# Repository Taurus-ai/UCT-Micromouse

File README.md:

# UCT-Micromouse EEE3088F PROJECT 2024 - POWER SUBMODULE
This is a repository for the power subsystem. The power substem is responsible for providing power to the micromouse design.
This design has 4 subcircuits which make up the subsytem:
1. Connectors - These provide interface to the other submodules. 
2. USB Power Supply - This provides external power to the circuit to charge the battery.
3. Battery charger - This cicuit mornitors the battery and charge it.
4. Motor Driver - This is a dual H-bridge motor driver circuit which drives 2 motors at desired current. 

This reporsitory includes the following files:
1. KiCAd project - This has the design of the pcb
2. BOM file - Bill of matertials for the components in the design
3. Datasheets - These are datasheets of the components used in the design.

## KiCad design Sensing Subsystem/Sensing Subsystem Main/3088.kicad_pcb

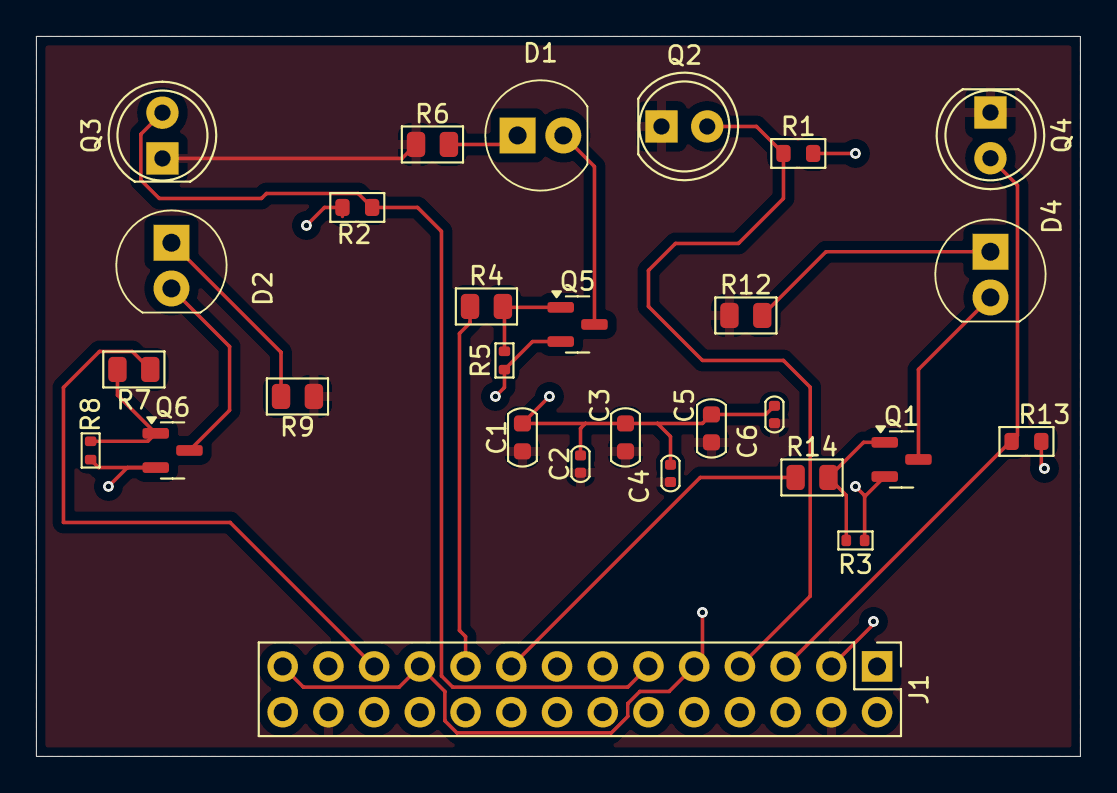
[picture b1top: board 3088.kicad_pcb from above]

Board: 2 copper layers, 58.0 x 40.0 mm, 28 parts (0 on the bottom side), 17 nets.

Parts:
C1, C3, C5: C_0603; C_0603_1608Metric
C2, C4, C6: C_0402; C_0402_1005Metric
D1, D2, D4: SFH_4544; LED_5mm_Radial
J1: Conn_02x14; PinHeader_2x14_P2.54mm_Vertical
Q1, Q5, Q6: AO3401A; SOT-23
Q2, Q3, Q4: BP103B; LED_D5.0mm_Clear
R1, R2, R13: R_0603; R_0603_1608Metric
R3, R5, R8: R_0402; R_0402_1005Metric
R4, R6, R7, R9, R12, R14: R_0805; R_0805_2012Metric

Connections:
GND: C1.2, C2.2, C3.2, C4.2, C5.2, C6.2, J1.3, J1.9, J1.15, J1.21, J1.27, Q1.2 (S), Q5.2 (S), Q6.2 (S), R1.2, R2.2, R3.1, R5.1, R8.1, R13.2
MCU: J1.17, R14.1
MCU1: J1.19, R4.1
MCU2: J1.23, R7.1
unnamed: D1.1, R6.2
unnamed: D2.1, R9.2
unnamed: D4.1, R12.2
unnamed: D4.2, Q1.3 (D)
unnamed: Q1.1 (G), R3.2, R14.2
unnamed: D1.2, Q5.3 (D)
unnamed: Q5.1 (G), R4.2, R5.2
unnamed: D2.2, Q6.3 (D)
unnamed: Q6.1 (G), R7.2, R8.2
V_out: J1.5, Q4.2 (E), R13.1
V_out1: J1.7, Q2.2 (E), R1.1
V_out2: J1.11, Q3.2 (E), R2.1
power: C1.1, C2.1, C3.1, C4.1, C5.1, C6.1, J1.4, J1.26, Q2.1 (C), Q3.1 (C), Q4.1 (C), R6.1, R9.1, R12.1

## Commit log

2024-04-07 Create POWER SUBMODULE
2024-04-07 Add files via upload
    This is a bill of mateterials files for the power submodule
2024-04-07 Add files via upload
    Datasheets for the coimponents used in the power submodule design
2024-04-07 Add files via upload
    Kicad files designs for the Power submodule
2024-04-17 Create Sensing Submodule
    This branch contains files pertaining to the sensing submodule.
2024-04-17 Create Sensing Submodule
    This branch contains files pertaining to the sensing module of the UCT micromouse project.
2024-04-20 Create Testing
2024-04-21 Format cleaned up
2024-04-21 Create Report
